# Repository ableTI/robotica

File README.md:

# About
This is the repository for all the files associated with, and used to create, a soccer robot for participation in the [Robocup](https://www.robocup.org/leagues/18). Made by students of the Mendelcollege, from team 'Mendel'. Our team consists of: Abel, Jits, Jorn, Lucas, Nathanaël, Ruben and Robin.

We will be participating in the Robocup Junior Soccer Lightweight 2:2. 2 Robots will play against 2 others on a field that resembles a human soccer field while both teams try to score in the opponents goal. There will be 2 rounds, each round will last 10 minutes with a 5 minutes break in between. One may only win with a 10 point difference or when at the end of the match they have more points. There will be a coin toss at the start of the game that will decide who can choose to either kick to ball or choose wich end the ball gets kicked to. The team that looses the coin toss gets the other option.
  
This is the Soccer Field. Official picture from the RoboCupJunior website.

This is our 3D model for our robot that will be playing soccer. It is made in Fusion by Nathanaël, Jorn and Jits. 

# Info:

  [Mendelcollege.nl](https://mendelcollege.nl/ontdek-je-talenten/robotica-en-beta/)

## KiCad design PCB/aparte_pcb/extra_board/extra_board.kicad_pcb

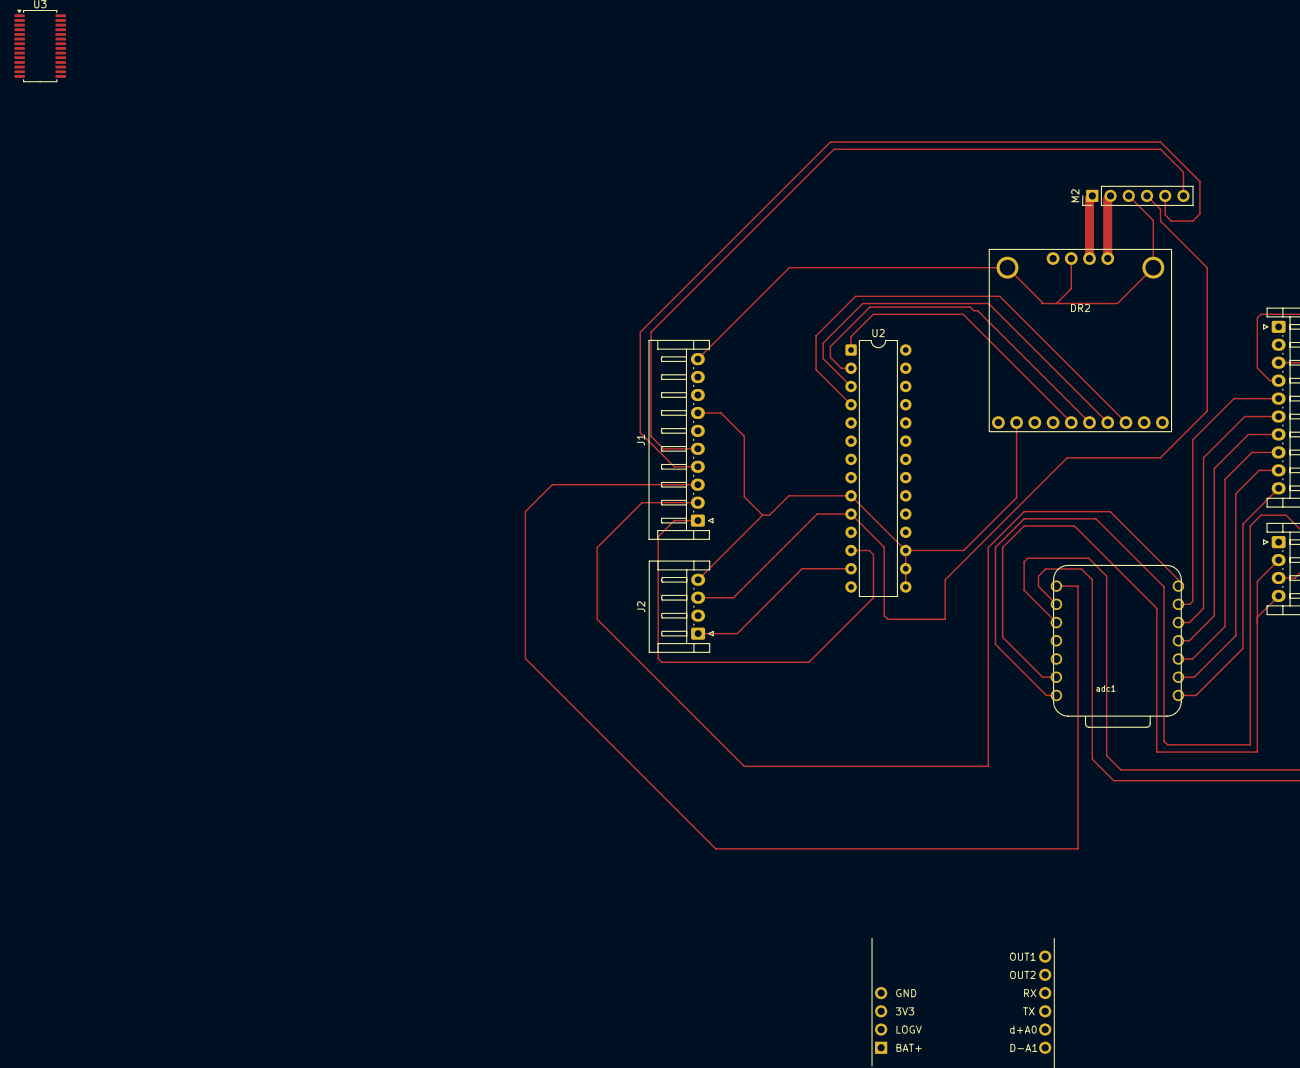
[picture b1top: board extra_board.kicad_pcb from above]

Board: 2 copper layers, 10 parts (0 on the bottom side), 30 nets.

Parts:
DR2: motordriver
J1, J3: Conn_01x10_Pin; JST_EH_S10B-EH_1x10_P2.50mm_Horizontal
J2, J4: Conn_01x04_Pin; JST_EH_S4B-EH_1x04_P2.50mm_Horizontal
M2: PinHeader_1x06_P2.54mm_Vertical
U1: soccer communinication module; soccer-communication-module
U2: MCP23017_SP; DIP-28_W7.62mm
U3: PCA9685PW; TSSOP-28_4.4x9.7mm_P0.65mm
adc1: Seeed Studio XIAO SAMD21; XIAO-SAMD21-SMD

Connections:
+5V: J2.3, J4.3, M2.4 (Vcc), U1.2 (logv), U3.14 (VSS), U3.25 (EXTCLK)
+12V: DR2.1 (VIN), U1.1 (BAt+)
/BLUE: J4.1, U3.12 (LED6)
/D+A0: J1.3, U1.6 (d+a0)
/D-A1: J1.2, U1.5 (d-a1)
/GREEN: J3.1, U3.11 (LED5)
/OUT1: J1.4, U1.10 (OUT1)
/OUT2: J1.5, U1.9 (OUT2)
/RED: J3.2, U3.10 (LED4)
/RX: J1.9, adc1.7 (PB08_A6_D6_TX)
/SCL: J1.10, U3.26 (SCL)
/SDA: J2.1, U3.27 (SDA)
/TX: J1.8, adc1.8 (PB09_A7_D7_RX)
/encA: J1.6, M2.5 (A_out)
/encB: J1.7, M2.6 (B_out)
/pr1: J3.10, adc1.1 (PA02_A0_D0)
/pr2: J3.9, adc1.2 (PA4_A1_D1)
/pr3: J3.8, adc1.3 (PA10_A2_D2)
/pr4: J3.7, adc1.4 (PA11_A3_D3)
/pr5: J3.6, adc1.5 (PA8_A4_D4_SDA)
/pr6: J3.5, adc1.6 (PA9_A5_D5_SCL)
/pr7: J3.4, adc1.9 (PA7_A8_D8_SCK)
/pr8: J3.3, adc1.10 (PA5_A9_D9_MISO)
GND: DR2.0 (screw), DR2.2 (GND), DR2.6 (GND), J1.1, J2.2, J2.4, J4.2, J4.4, M2.3 (GND), U1.4 (gnd), U2.9 (VDD), U2.15 (A0), U2.16 (A1), U2.17 (A2), U3.1 (A0), U3.2 (A1), U3.3 (A2), U3.4 (A3), U3.5 (A4), U3.22 (LED15), U3.24 (A5), U3.28 (VDD), adc1.13 (GND)
unnamed: DR2.9 (EN), U2.1 (GPB0), U3.6 (LED0)
unnamed: DR2.10 (ENB), U2.2 (GPB1), U3.7 (LED1)
unnamed: DR2.4 (OUT1), M2.2 (MotorPW)
unnamed: DR2.3 (OUT2), M2.1 (MotorPW)
unnamed: DR2.12 (PWM1), U2.4 (GPB3), U3.9 (LED3)
unnamed: DR2.11 (PWM2), U2.3 (GPB2), U3.8 (LED2)

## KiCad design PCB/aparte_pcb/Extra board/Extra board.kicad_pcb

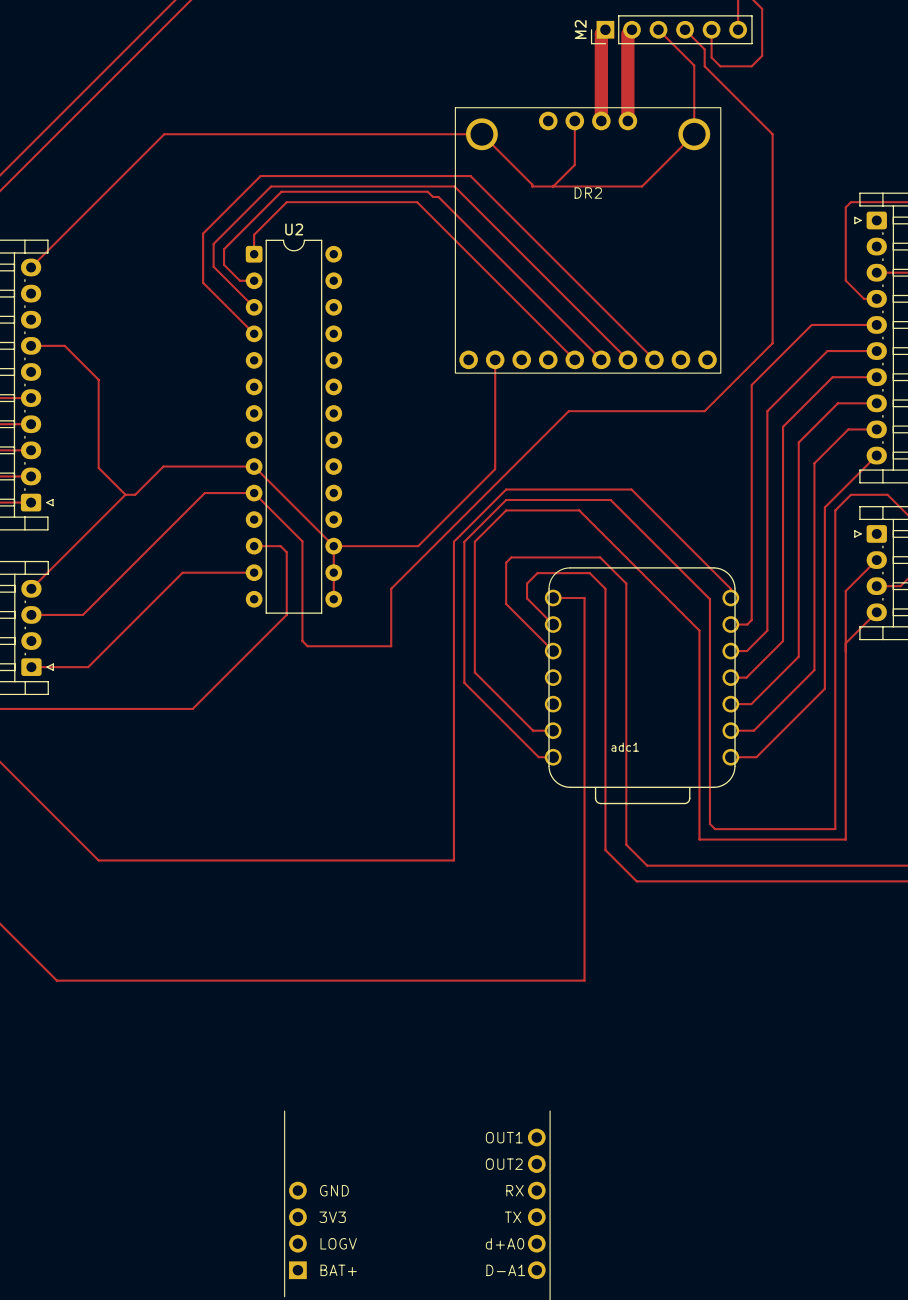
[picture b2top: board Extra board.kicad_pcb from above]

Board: 2 copper layers, 9 parts (0 on the bottom side), 25 nets.

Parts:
DR2: motordriver
J1, J3: Conn_01x10_Pin; JST_EH_S10B-EH_1x10_P2.50mm_Horizontal
J2, J4: Conn_01x04_Pin; JST_EH_S4B-EH_1x04_P2.50mm_Horizontal
M2: PinHeader_1x06_P2.54mm_Vertical
U1: soccer-communication-module
U2: MCP23017_SP; DIP-28_W7.62mm
adc1: Seeed Studio XIAO SAMD21; XIAO-SAMD21-SMD

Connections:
5v: J2.3, J4.3, M2.4 (Vcc), U1.2 (logv), U2.10 (VSS), adc1.14 (5V)
D+A0: J1.7, U1.6 (d+a0)
D-A1: J1.8, U1.5 (d-a1)
GND: DR2.0 (screw), DR2.2 (GND), DR2.6 (GND), J1.9, J1.10, J2.2, J2.4, J4.2, J4.4, M2.3 (GND), U1.4 (gnd), U2.9 (VDD), U2.15 (A0), U2.16 (A1), U2.17 (A2), adc1.13 (GND)
unnamed: DR2.9 (EN), U2.1 (GPB0)
unnamed: DR2.10 (ENB), U2.2 (GPB1)
unnamed: DR2.4 (OUT1), M2.2 (MotorPW)
unnamed: DR2.3 (OUT2), M2.1 (MotorPW)
unnamed: DR2.12 (PWM1), U2.4 (GPB3)
unnamed: DR2.11 (PWM2), U2.3 (GPB2)
OUT2: J1.6, U1.9 (OUT2)
RX: J1.2, adc1.7 (PB08_A6_D6_TX)
SCL: J1.1, U2.12 (SCK)
SDA: J2.1, U2.13 (SDA)
TX: J1.3, adc1.8 (PB09_A7_D7_RX)
encA: J1.4, M2.5 (A_out)
encB: J1.5, M2.6 (B_out)
pr1: J3.10, adc1.1 (PA02_A0_D0)
pr2: J3.9, adc1.2 (PA4_A1_D1)
pr3: J3.8, adc1.3 (PA10_A2_D2)
pr4: J3.7, adc1.4 (PA11_A3_D3)
pr5: J3.6, adc1.5 (PA8_A4_D4_SDA)
pr6: J3.5, adc1.6 (PA9_A5_D5_SCL)
pr7: J3.4, adc1.9 (PA7_A8_D8_SCK)
pr8: J3.3, adc1.10 (PA5_A9_D9_MISO)

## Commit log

2025-05-26 extra PCB changes
    Multi-line description of commit,
    feel free to be detailed.
2025-05-26 almost finished extra pcb
    The pcb is designed to be single layerd for simplisity, but there are still two unconnected lines, GND and 5V are now both in two seperate sections. Can connect via an wire or update the PCB. Will no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
2025-05-27 zephyr
    Multi-line description of commit,
    feel free to be detailed.
2025-05-28 sSubject line (try to keep under 50 characters)
    Multi-line description of commit,
    feel free to be detailed.
2025-05-29 encoder zephyr
    Think this should work to use the encoder but cna only build not upload, need to wait till monday till i can test it with a robot.
2025-05-29 Communication module.
    Added Communication module to extra PCB, but the power requerments are either our battery power or 3v, but current lines only allow 5v, so either new lines or an power conversion component.
    Need to discuss best option with team.
    Also TX/RX lines optional but not available. I2C to UART module?
    Also need to discuss.
2025-05-29 setup script added for linux begin will cont later.
2025-05-30 Setup script added selection menu
    There is a syntacs error in the menu somwere but have no time now to fix it, so commiting it.
    Will probly fix later today.
2025-05-30 Fixed previous error, need to finish later.
    need option menu to have effect an git setup needs to be finished
    Importing the GPG and SSH keys need to be done via an secure way, don't yet know how. posibly an encripted file that includes the files.
2025-05-31 Setup.sh completed, need to test.
2025-06-01 think finished scrpt, testing now
    There are now three scripts,
    1) to select the script
    2) an automated install script
    3) an guided installmet script
    will need to test, but willl push first to easly acces on my other pc where i will test
    will also give garanteed error on first passwd try, because i can and nobody find out and nobody will read the code anyways or these commits.
2025-06-01 Update createlivedrive.md
    added enters
2025-06-01 Needed to use raw files suerd gt html page
    Multi-line description of commit,
    feel free to be detailed.
2025-06-01 fixed option 3 actualy exiting, 2--> no sudo, says how to exit now, and check internet with ping no wget.
    micro pushes becouse i need to download it on my other maching via the manual in the folder
2025-06-01 createed an readme instead of script, because for unknown reason apps installed via apt will not wok via bash script.
2025-06-01 minor changes
2025-06-01 Rename createlivedrive.md to readme.md
2025-06-04 multiple things
2025-06-04 Add files via upload
    New design
2025-06-04 test test Subject line (try to keep under 50 characters)
    Multi-line description of commit,
    feel free to be detailed.
    Please also include who worked on the commit.
    [Issue: X]
2025-06-09 Changes to PCB
    added some symboles did some changes.
2025-06-12 recenltly removed three commit becouse it included files that shouldn't be included.
    Did reset hard,
    localy unstaged commits, deleted files and recommited the good files.
    think this is all i did since,
    -changed extra PCB name to bave and _ instead of a space so i dont have to use ""
    -added button and led to teensy41 goaly overlay
    -started on PWM, not complete
2025-06-12 Update LICENSE
    Changed to eupl and give right to mendelcollege
2025-06-12 Fixed some errors
2025-06-17 Update LICENSE
2025-06-18 pre robotica commit
    Multi-line description of commit,
    feel free to be detailed.
